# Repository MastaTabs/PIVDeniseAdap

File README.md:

# PIV Denise Adapter

No free or missing video slot in your ECS/OCS system and want to fully  use a PicassoIV ?

Then this adapter pcb comes to the rescue which replaces the PIV's FlickerFixer break off section.

Important! The break off part of the PIV must be removed  to use this in place off it!

The design isn't proven yet but was created from the original schematics and PCB layout.

### License
The "PIV Denise Adapter" documentation, including the design itself, is copyright © MastaTabs (Tobias Seiler) 2020.

"PIV Denise Adapter" is Open Hardware licensed under the CERN OHL v. 1.2.

You may redistribute and modify this documentation under the terms of the CERN OHL v.1.2. This documentation is distributed as is and WITHOUT ANY EXPRESS OR IMPLIED WARRANTIES whatsoever with respect to its functionality, operability or use, including, without limitation, any implied warranties OF MERCHANTABILITY, SATISFACTORY QUALITY, FITNESS FOR A PARTICULAR PURPOSE or infringement. We expressly disclaim any liability whatsoever for any direct, indirect, consequential, incidental or special damages, including, without limitation, lost revenues, lost profits, losses resulting from business interruption or loss of data, regardless of the form of action or legal theory under which the liability may be asserted, even if advised of the possibility or likelihood of such damages.

A copy of the full license is included in file LICENSE.pdf, please refer to it for applicable conditions. In order to properly deal with its terms, please see file LICENSE_HOWTO.pdf.

The contact points for information about manufactured Products (see section 4.2) are listed in file PRODUCT.md.

Any modifications made by Licensees (see section 3.4.b) shall be recorded in file CHANGES.md.

The Documentation Location of the original project is https://github.com/MastaTabs/PIVDeniseAdap.

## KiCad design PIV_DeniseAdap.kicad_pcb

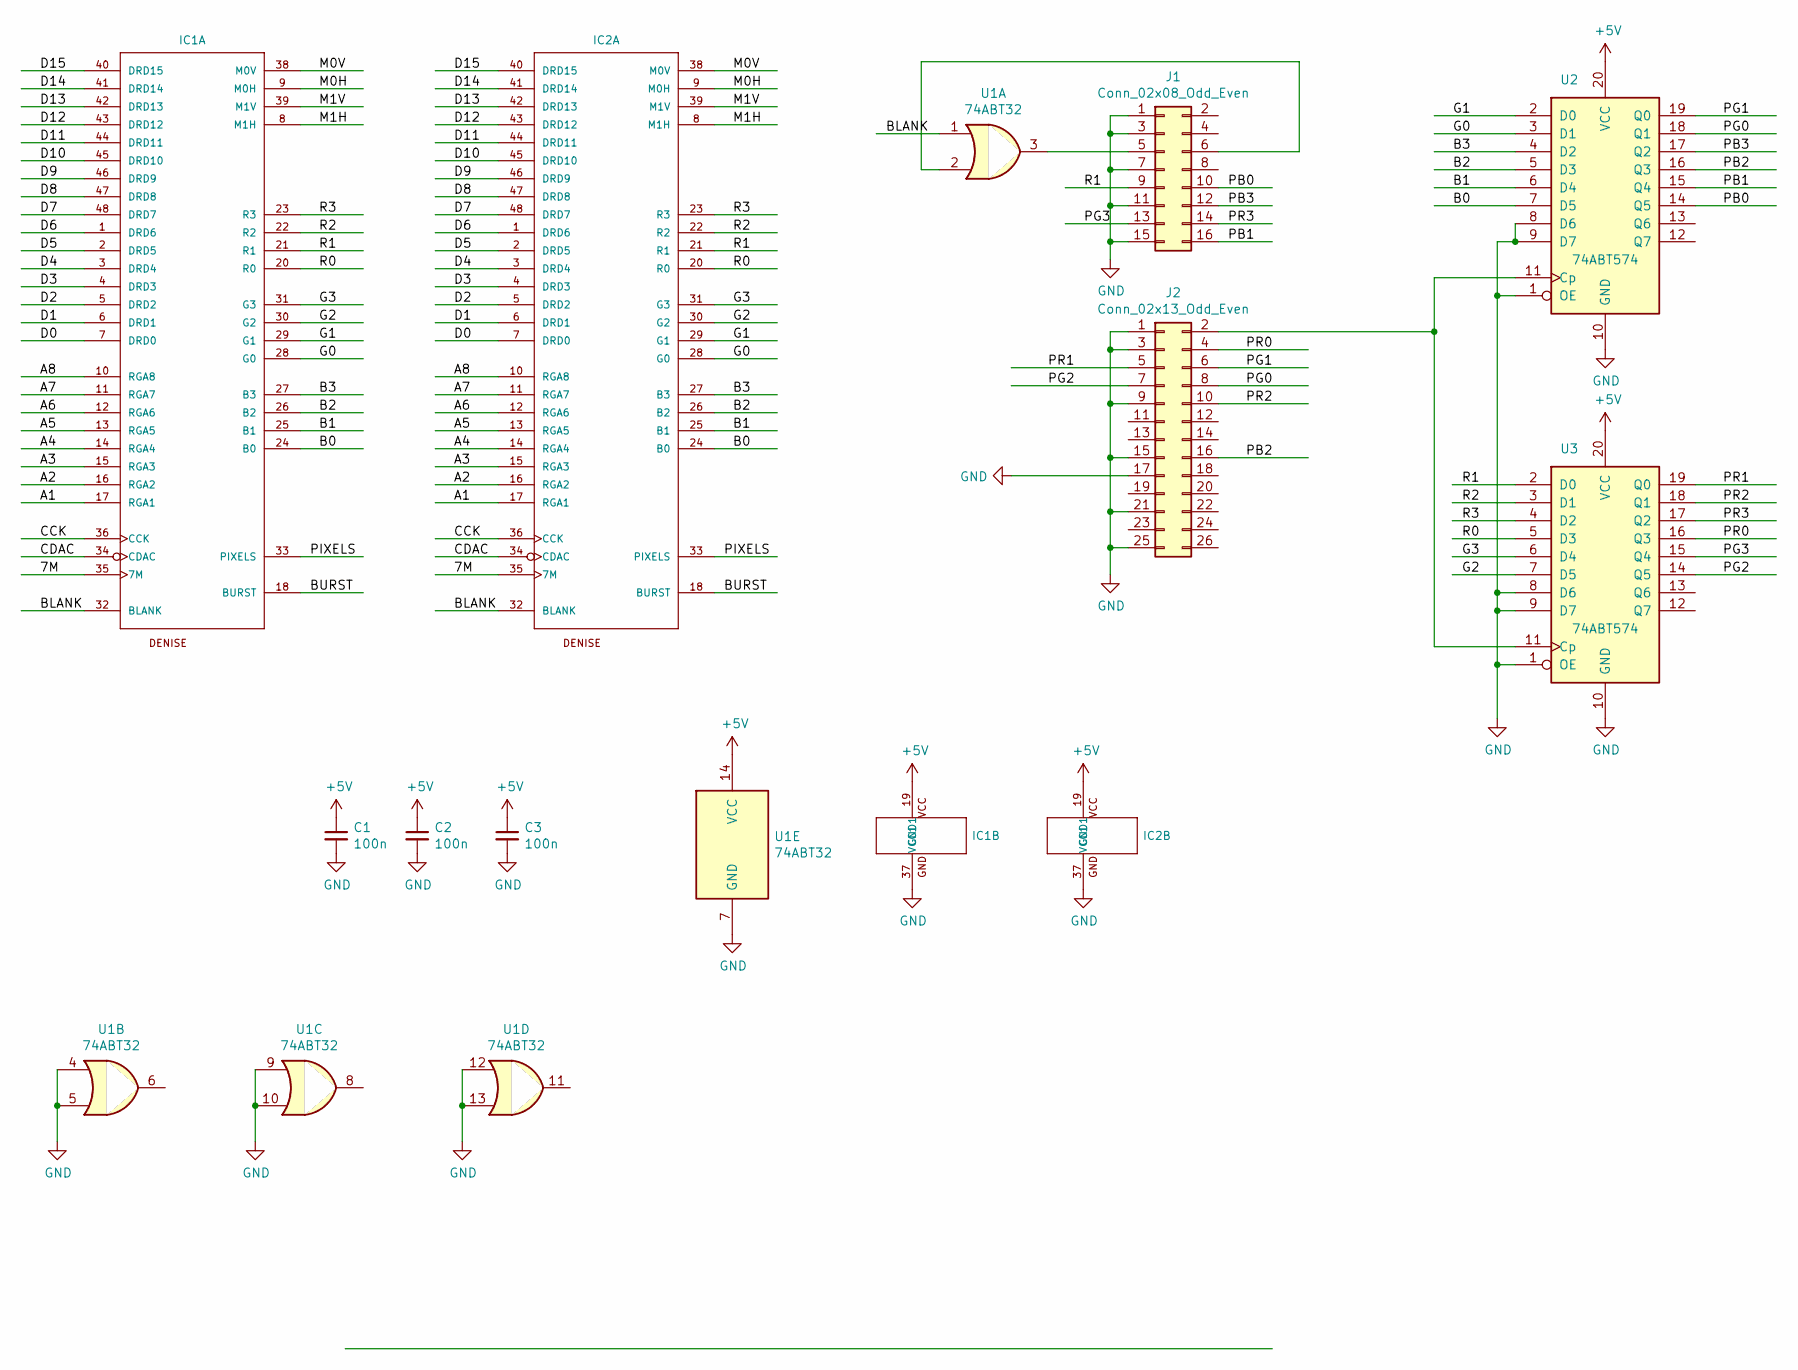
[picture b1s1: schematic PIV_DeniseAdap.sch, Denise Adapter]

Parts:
C1, C2, C3: 100n; C_0805_HandSoldering
IC1, IC2: DENISE_DIP; Amiga-DIP48-DENISE
J1: Conn_02x08_Odd_Even; Pin_Header_Straight_2x08_Pitch2.54mm
J2: Conn_02x13_Odd_Even; Pin_Header_Straight_2x13_Pitch2.54mm
U1: 74ABT32; SN74ABT125NSR
U2, U3: 74ABT574; SN74ABT574ANSR

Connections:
+5V: C1.1, C2.1, C3.1, IC1.19 (VCC1), IC2.19 (VCC1), U1.14 (VCC), U2.20 (VCC), U3.20 (VCC)
/7M: IC1.35 (7M), IC2.35 (7M)
/A1: IC1.17 (RGA1), IC2.17 (RGA1)
/A2: IC1.16 (RGA2), IC2.16 (RGA2)
/A3: IC1.15 (RGA3), IC2.15 (RGA3)
/A4: IC1.14 (RGA4), IC2.14 (RGA4)
/A5: IC1.13 (RGA5), IC2.13 (RGA5)
/A6: IC1.12 (RGA6), IC2.12 (RGA6)
/A7: IC1.11 (RGA7), IC2.11 (RGA7)
/A8: IC1.10 (RGA8), IC2.10 (RGA8)
/B0: IC1.24 (B0), IC2.24 (B0), U2.7 (D5)
/B1: IC1.25 (B1), IC2.25 (B1), U2.6 (D4)
/B2: IC1.26 (B2), IC2.26 (B2), U2.5 (D3)
/B3: IC1.27 (B3), IC2.27 (B3), U2.4 (D2)
/BLANK: IC1.32 (BLANK), IC2.32 (BLANK), U1.1
/BURST: IC1.18 (BURST), IC2.18 (BURST)
/CCK: IC1.36 (CCK), IC2.36 (CCK)
/CDAC: IC1.34 (CDAC), IC2.34 (CDAC)
/D0: IC1.7 (DRD0), IC2.7 (DRD0)
/D1: IC1.6 (DRD1), IC2.6 (DRD1)
/D2: IC1.5 (DRD2), IC2.5 (DRD2)
/D3: IC1.4 (DRD3), IC2.4 (DRD3)
/D4: IC1.3 (DRD4), IC2.3 (DRD4)
/D5: IC1.2 (DRD5), IC2.2 (DRD5)
/D6: IC1.1 (DRD6), IC2.1 (DRD6)
/D7: IC1.48 (DRD7), IC2.48 (DRD7)
/D8: IC1.47 (DRD8), IC2.47 (DRD8)
/D9: IC1.46 (DRD9), IC2.46 (DRD9)
/D10: IC1.45 (DRD10), IC2.45 (DRD10)
/D11: IC1.44 (DRD11), IC2.44 (DRD11)
/D12: IC1.43 (DRD12), IC2.43 (DRD12)
/D13: IC1.42 (DRD13), IC2.42 (DRD13)
/D14: IC1.41 (DRD14), IC2.41 (DRD14)
/D15: IC1.40 (DRD15), IC2.40 (DRD15)
/G0: IC1.28 (G0), IC2.28 (G0), U2.3 (D1)
/G1: IC1.29 (G1), IC2.29 (G1), U2.2 (D0)
/G2: IC1.30 (G2), IC2.30 (G2), U3.7 (D5)
/G3: IC1.31 (G3), IC2.31 (G3), U3.6 (D4)
/M0H: IC1.9 (M0H), IC2.9 (M0H)
/M0V: IC1.38 (M0V), IC2.38 (M0V)
/M1H: IC1.8 (M1H), IC2.8 (M1H)
/M1V: IC1.39 (M1V), IC2.39 (M1V)
/PB0: J1.10, U2.14 (Q5)
/PB1: J1.16, U2.15 (Q4)
/PB2: J2.16, U2.16 (Q3)
/PB3: J1.12, U2.17 (Q2)
/PG0: J2.8, U2.18 (Q1)
/PG1: J2.6, U2.19 (Q0)
/PG2: J2.7, U3.14 (Q5)
/PG3: J1.13, U3.15 (Q4)
/PIXELS: IC1.33 (PIXELS), IC2.33 (PIXELS)
/PR0: J2.4, U3.16 (Q3)
/PR1: J2.5, U3.19 (Q0)
/PR2: J2.10, U3.18 (Q1)
/PR3: J1.14, U3.17 (Q2)
/R0: IC1.20 (R0), IC2.20 (R0), U3.5 (D3)
/R1: IC1.21 (R1), IC2.21 (R1), J1.9, U3.2 (D0)
/R2: IC1.22 (R2), IC2.22 (R2), U3.3 (D1)
/R3: IC1.23 (R3), IC2.23 (R3), U3.4 (D2)
GND: C1.2, C2.2, C3.2, IC1.37 (GND1), IC2.37 (GND1), J1.1, J1.3, J1.7, J1.11, J1.15, J2.1, J2.3, J2.9, J2.15, J2.17, J2.21, J2.25, U1.4, U1.5, U1.7 (GND), U1.9, U1.10, U1.12, U1.13, U2.1 (OE), U2.8 (D6), U2.9 (D7), U2.10 (GND), U3.1 (OE), U3.8 (D6), U3.9 (D7), U3.10 (GND)
unnamed: J1.5, U1.3
unnamed: J1.6, U1.2
unnamed: J2.2, U2.11 (Cp), U3.11 (Cp)

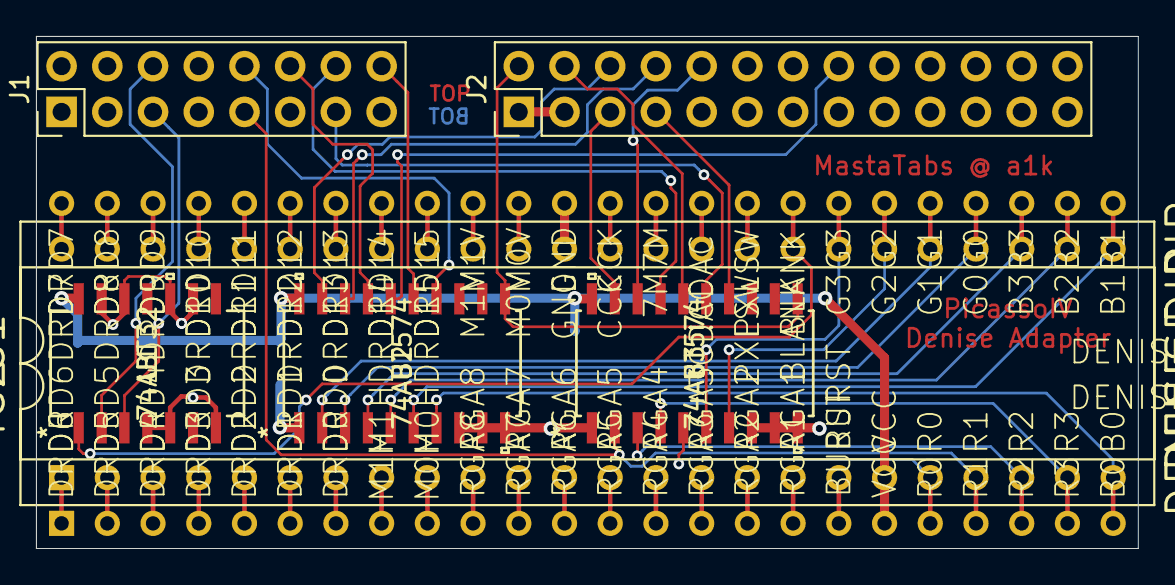
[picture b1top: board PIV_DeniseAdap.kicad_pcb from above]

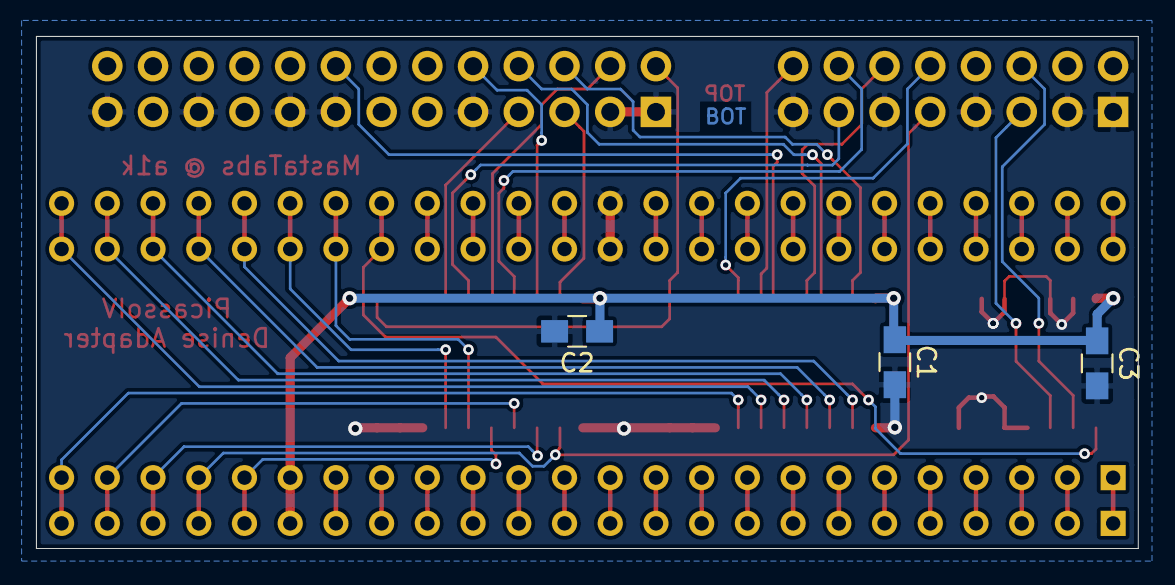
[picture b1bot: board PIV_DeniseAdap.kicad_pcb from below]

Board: 2 copper layers, 61.2 x 28.4 mm, 10 parts (3 on the bottom side), 63 nets.

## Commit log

2020-05-31 fixed README

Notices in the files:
parts and their libraries:
Copyright 2016 Accelerated Designs. All rights reserved.
